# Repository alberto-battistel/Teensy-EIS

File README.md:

# Teensy-EIS

At the moment this git is still slightly chaotic, but it is getting better.
The idea is to use the two ADCs of the Teensy 3.6 (pjrc.com) to aquire data and the DAC to create the perturbation (sinus/multisine) to work as an impedance analyzer. All controlled by a PC using Python, which also make the analysis part. We have an analog front-end for voltage shift (Teensy works 0-3.3V both ADC and DAC) to connect to the real potentiostat. This is tested and works.

## 1 - ADC-DAC
ADC-DAC.ino and readFromPython.py work together. They are THE Teensy-EIS programs. CalculateParameters.m helps to make the parameters to feed in Python.

## 2 - Examples
In ADC-DAC there are examples of the part of the ADC-DAC.ino. DAC is for the DAC and PingPong manages the serial communication with the PC. They are more or less the most updated or the same as in ADC-DAC.ino.

## 3 - Regarding the DAC
The signal for the DAC is generated through a Matlab/GNU Octave/Scilab script. (Generate_DAC_vector). 

## 4 - Analog front-end
In analog front-end there is all about the core of the voltage shift. All the analog interface with the instrument is based on four INA128. They are very flexible pieces. There is no schematic for the power stage and activation of the signal line, but the elements are in the two PDF.

## 5 - Control flow
In Schematics there are the diagrams of the programs. At the moment only the part for the aquisition, which is the most complex. In summary, the Teensy can aquire infinite amount of data which are streamed in blocks to the PC. Python can handle easily several milions data points. 

## 6 - pointer?
pointers-reference-test contains a couple of examples about passing by reference or by pointer to a function. Not fundamental for the rest, just to remember.

------------------------------------
# Version list:

## Version 1.00
Fully operational tidy up version.

## Version 0.99
Fully operational prototype, both for the programing side and for the analog side. 

------------------------------------
# Bug List:
So we can keep track of what needs to be fixed

-To be filled (Priority: 1)

------------------------------------
# Future Feature List:

## Version 1.1?
what shall we implement next?

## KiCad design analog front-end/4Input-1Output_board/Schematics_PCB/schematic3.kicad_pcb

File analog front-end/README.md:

# Analog front-end
The analog front-end interfaces the *Teensy* to the instrument (potentiostat). It serves as conditioning of the signals. It mainly provides low impedance for the inputs, level shift (*Teensy* is 0-3.3V), and some degree of rejection for ground loops (still to understand a bit better). It also features an independent power stage (USB compatible) to handle bipolar signals.

## Signal conditioning
At the moment the conditioning is build on 4 **INAs 128** (Instrumentation amplifiers) from Texas Instruments. They are flexible building blocks featuring low noise, low distortion, easy level shift, and high impedance inputs (10 GOhm). Two INAs are used to buffer, level shift, and shrink the DAC (digital to analog converter) of the *Teensy* and the other two are for level shifting of the inputs of the two ADCs (analog to digital converter). 
Analog filtering can be easily attached to the INAs.
**4Input-1Output_board** contains the full design (schematics and printed circuit board layout with bill of components) to build up the signal conditioning part. It is a very flexible board. We also employ it for *additional reference electrode probes* in electrochemical cells or to *break groud loops*.

## Power
The power stage is based on a **DC-DC converter** (*NMA0515SC* from Murata). It takes 5 V as input and provides +/- 15 V. It may be connected to the *Teensy* and take power from the same USB cable, but we did not test this yet. The bipolar voltage is used to power the INAs. The positive rail is also used to hold a normally open **signal relay** (*MT2 Relay* from AXICOM). This relay is controlled by a digital pin of the *Teensy* through a transistor (*2N3904*) and it is necessary to cut the DAC line from the *Teensy* toward the instrument so that unwanted signals cannot be injected (for example when you turn on the *Teensy*...).

## State of the material
At the moment the schematics and the PCB layout signal conditioning part is available in **4Input-1Output_board**, but we may come out with a more practical design later. 
**Complete_analog_front-end.pro** (*KiCAD project* in **Design_schematics**) contains the *functional design* of the project with the fundamental connections between the *Teensy* and the analog front-end and the power stage.

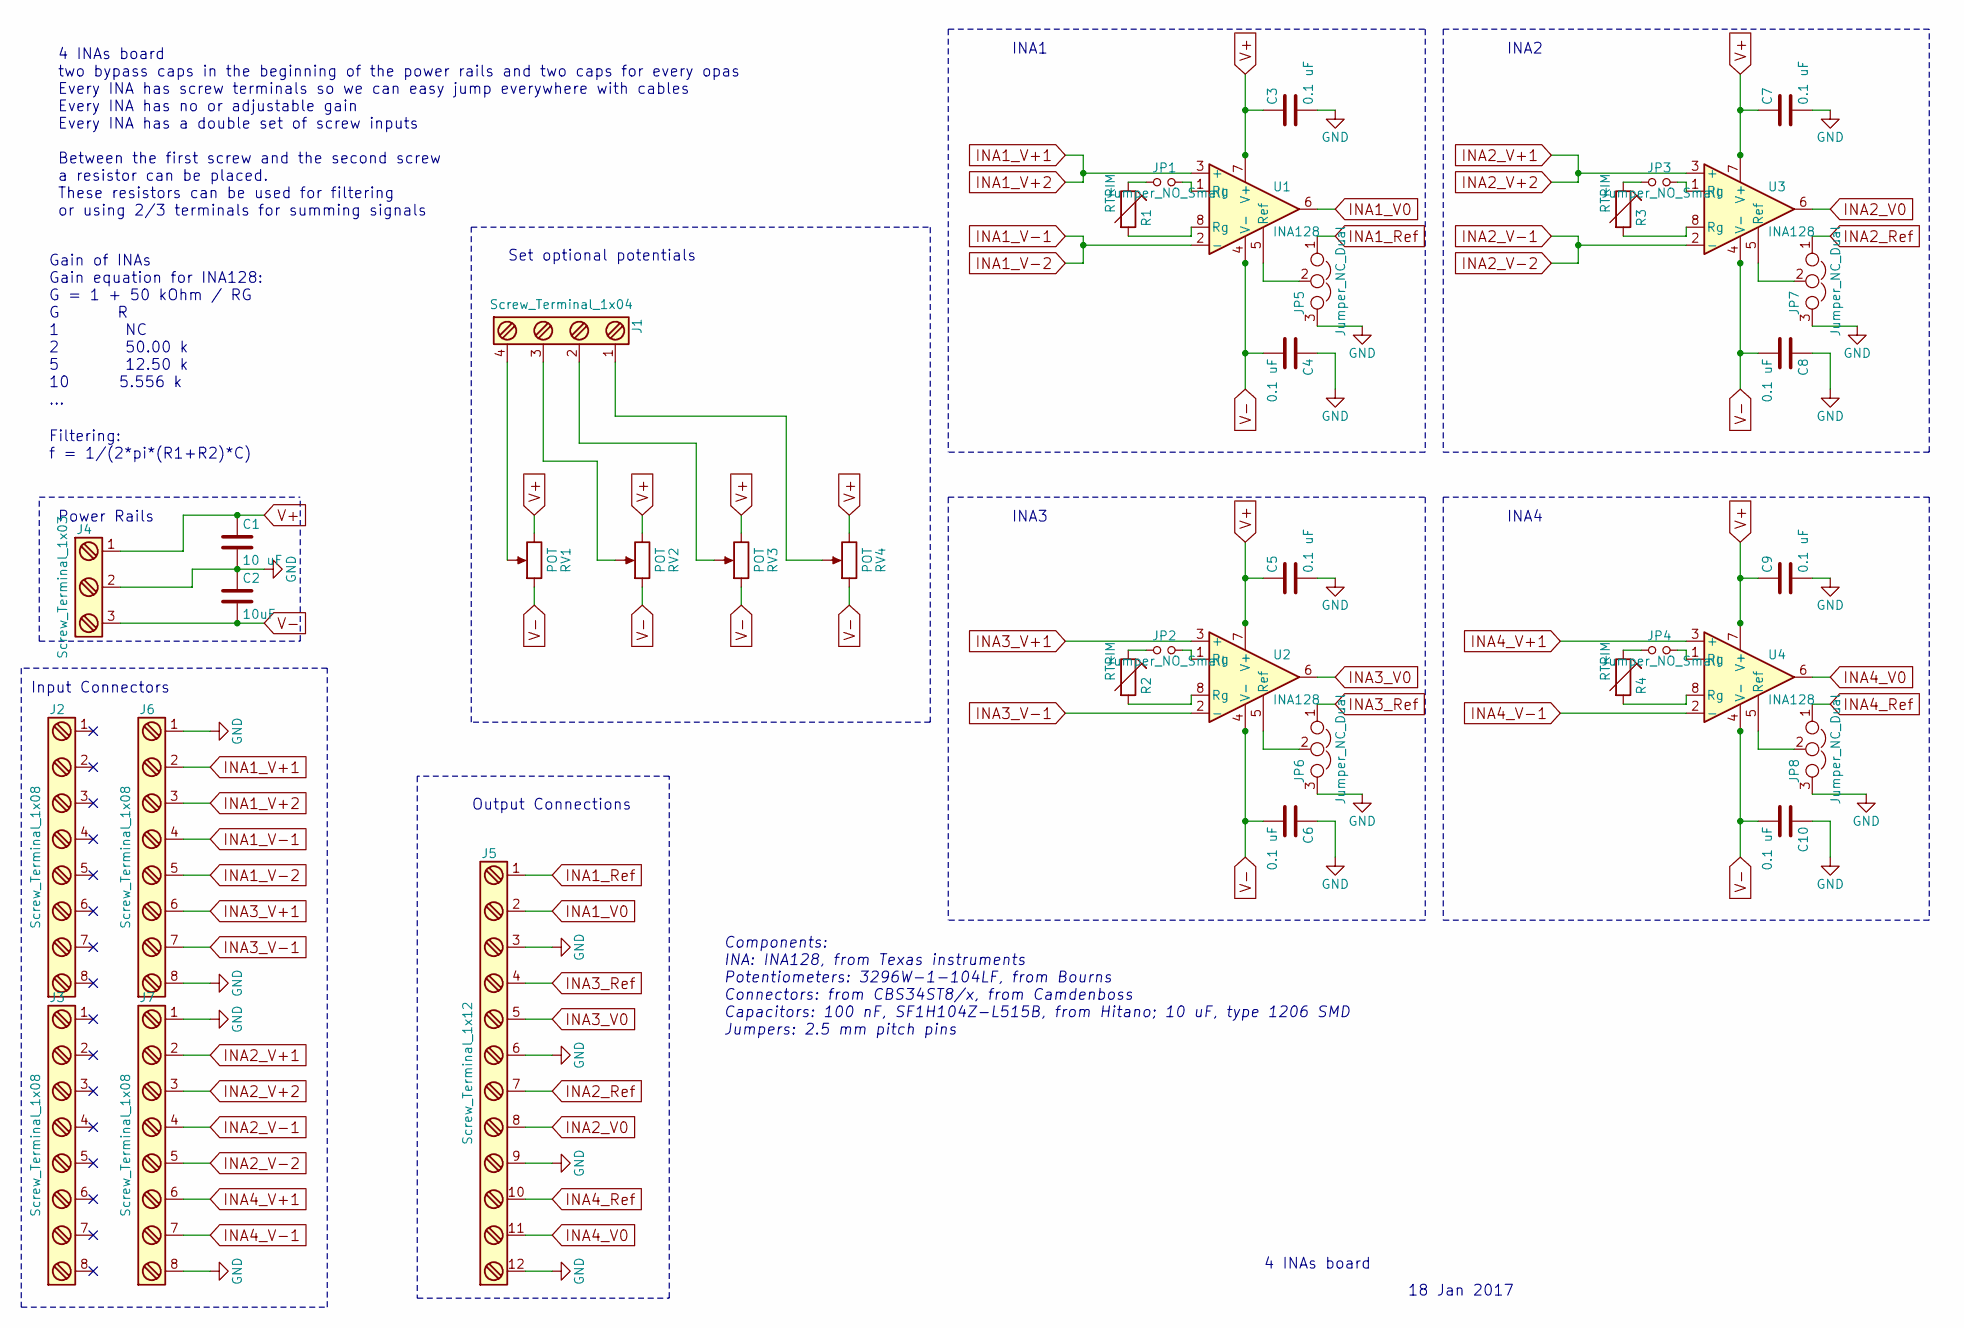
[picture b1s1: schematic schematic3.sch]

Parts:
C1: 10 uF; C_0603_HandSoldering
C2: 10uF; C_0603_HandSoldering
C3, C4, C5, C6, C7, C8, C9, C10: 0.1 uF; C_Disc_D5.0mm_W2.5mm_P5.00mm
J1: Screw_Terminal_1x04; Camdenboss_Screw_terminal_4x9.5mm
J2, J3, J6, J7: Screw_Terminal_1x08; Camdenboss_Screw_terminal_8x9.5mm
J4: Screw_Terminal_1x03; Camdenboss_Screw_terminal_3x9.5mm
J5: Screw_Terminal_1x12; Camdenboss_Screw_terminal_12x9.5mm
JP1, JP2, JP3, JP4: Jumper_NO_Small; JST_EH_B02B-EH-A_02x2.50mm_Straight
JP5, JP6, JP7, JP8: Jumper_NC_Dual; JST_EH_B03B-EH-A_03x2.50mm_Straight
R1, R2, R3, R4: RTRIM; Potentiometer_Bourns_3296W_3-8Zoll_Inline_ScrewUp
RV1, RV2, RV3, RV4: POT; Potentiometer_Bourns_3296W_3-8Zoll_Inline_ScrewUp
U1, U2, U3, U4: INA128; DIP-8_W7.62mm_Socket

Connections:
GND: C1.2, C2.1, C3.2, C4.1, C5.2, C6.1, C7.2, C8.1, C9.2, C10.1, J4.2, J5.3, J5.6, J5.9, J5.12, J6.1, J6.8, J7.1, J7.8, JP5.3, JP6.3, JP7.3, JP8.3
INA1_Ref: J5.1, JP5.1
INA1_V0: J5.2, U1.6
INA1_V+1: J6.2, J6.3, U1.3 (+)
INA1_V-1: J6.4, J6.5, U1.2 (-)
INA2_Ref: J5.7, JP7.1
INA2_V0: J5.8, U3.6
INA2_V+1: J7.2, J7.3, U3.3 (+)
INA2_V-1: J7.4, J7.5, U3.2 (-)
INA3_Ref: J5.4, JP6.1
INA3_V0: J5.5, U2.6
INA3_V+1: J6.6, U2.3 (+)
INA3_V-1: J6.7, U2.2 (-)
INA4_Ref: J5.10, JP8.1
INA4_V0: J5.11, U4.6
INA4_V+1: J7.6, U4.3 (+)
INA4_V-1: J7.7, U4.2 (-)
unnamed: J1.1, RV4.2
unnamed: J1.2, RV3.2
unnamed: J1.3, RV2.2
unnamed: J1.4, RV1.2
unnamed: JP1.1, R1.1
unnamed: JP1.2, U1.1 (Rg)
unnamed: JP2.1, R2.1
unnamed: JP2.2, U2.1 (Rg)
unnamed: JP3.1, R3.1
unnamed: JP3.2, U3.1 (Rg)
unnamed: JP4.1, R4.1
unnamed: JP4.2, U4.1 (Rg)
unnamed: JP5.2, U1.5 (Ref)
unnamed: JP6.2, U2.5 (Ref)
unnamed: JP7.2, U3.5 (Ref)
unnamed: JP8.2, U4.5 (Ref)
unnamed: R1.2, U1.8 (Rg)
unnamed: R2.2, U2.8 (Rg)
unnamed: R3.2, U3.8 (Rg)
unnamed: R4.2, U4.8 (Rg)
V+: C1.1, C3.1, C5.1, C7.1, C9.1, J4.1, RV1.3, RV2.3, RV3.3, RV4.3, U1.7 (V+), U2.7 (V+), U3.7 (V+), U4.7 (V+)
V-: C2.2, C4.2, C6.2, C8.2, C10.2, J4.3, RV1.1, RV2.1, RV3.1, RV4.1, U1.4 (V-), U2.4 (V-), U3.4 (V-), U4.4 (V-)

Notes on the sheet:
Gain of INAs Gain equation for INA128: G = 1 + 50 kOhm / RG G R 1 NC 2 50.00 k 5 12.50 k 10 5.556 k ...
INA1
Power Rails
4 INAs board two bypass caps in the beginning of the power rails and two caps for every opas Every INA has screw terminals so we can easy jump everywhere with cables Every INA has no or adjustable gain Every INA has a double set of screw inputs Between the first screw and the second screw a resisto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
Set optional potentials
Filtering: f = 1/(2*pi*(R1+R2)*C)
INA2
INA4
4 INAs board
18 Jan 2017
INA3
Input Connectors
Output Connections
Components: INA: INA128, from Texas instruments Potentiometers: 3296W-1-104LF, from Bourns Connectors: from CBS34ST8/x, from Camdenboss Capacitors: 100 nF, SF1H104Z-L515B, from Hitano; 10 uF, type 1206 SMD Jumpers: 2.5 mm pitch pins

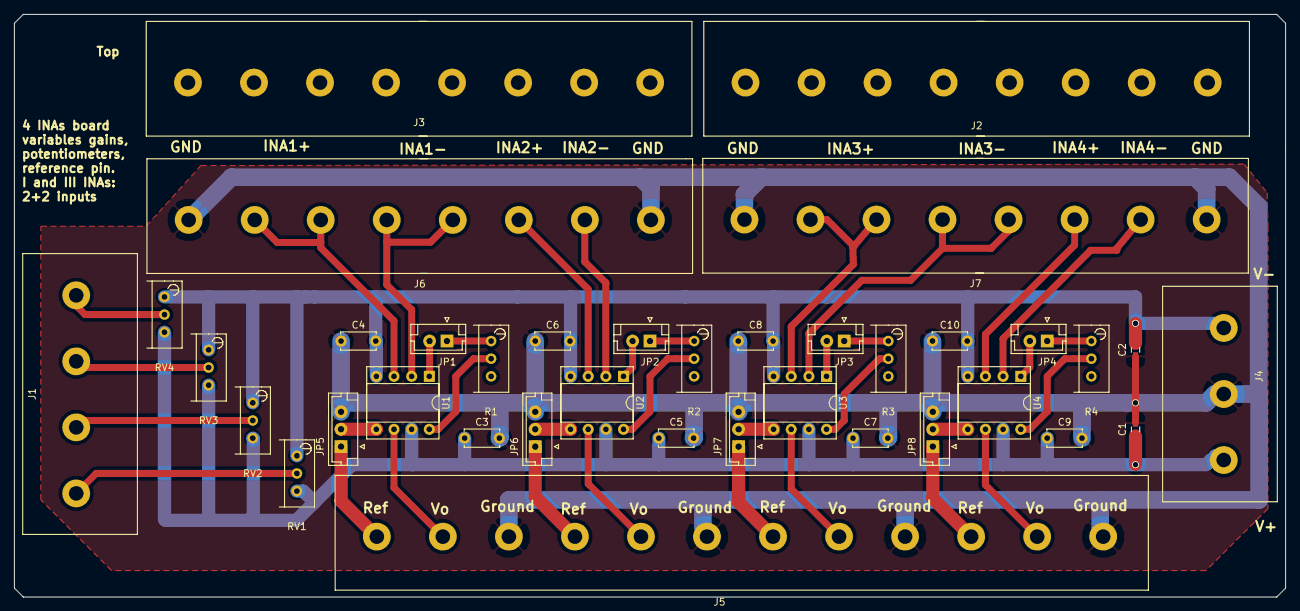
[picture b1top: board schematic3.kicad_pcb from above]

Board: 2 copper layers, 182.9 x 83.8 mm, 37 parts (0 on the bottom side), 39 nets.

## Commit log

2017-08-25 first commit, really the previous was an error
2017-08-26 justTest and readFromPython can pass data
2017-08-27 put a bit of order and add example for DAC
2017-08-27 updated datalogger_2ch with byte stream
2017-08-28 ADC-DAC: DAC and ADC work fine together, but there are some problems with the stream of data toward python.
2017-08-28 ADC-DAC starts to work, teensy streams to python, but I lose synchronization sometimes
2017-08-29 ADC-DAC works fine with one ADC, python catches all the stream
2017-08-30 Test commit by Chris
2017-08-30 ADC-DAC now can stream both channels, but StreamData needs to be corrected...
2017-08-31 collecting things into function in ADC-DAC
2017-08-31 I implemented pointers in ADC-DAC, but i dont understand what I am streaming. If both adc are connected I see two nice equal sinus. If only one of the two is disconnected I see strange noise.I have n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
2017-09-04 Starting to collect things for the analog front-end.
2017-09-04 schematics
2017-09-05 Added some organizational stuff(bug list, future feature list), to help contributors know where to focus.
2017-09-05 Create development_list.txt
    list of things to implement
2017-09-05 PingPong old style
2017-09-05 fix Parameters passing, but I do not understand header and source files.
2017-09-06 Update development_list.txt
    modified development_list.txt adding the transistor part
2017-09-06 Implemented header file for PingPong, not properly done (I don't have a cpp file), but it works.
2017-09-06 DAC.h done and working
2017-09-06 I did a mess with the file in the previous commit and now I fixed. I also moved PingPong in ADC-DAC.
2017-09-06 I had a pc failure, but now I am back. I integrated PingPong.h into ADC-DAC.ino. Ready for the loops.
2017-09-06 All the functions definition have been moved out of ADC-DAC.
2017-09-06 Create LICENSE
    Added LICENSE
2017-09-06 fixed a couple of bugs
2017-09-06 added DefaultParameters.h. ADC-DAC.ino can loopgit add . maybe some comments are missing or needed...
2017-09-06 Teensy and Python are looping together! Still very rough, but working.
2017-09-07 I need to fix python to calculate Z...
2017-09-07 python and teensy works together, I made a matlab script to calculate the Paramerters. I have problems with the PDB, I think.
2017-09-07 Teensy and python work together. CalculateParameters.m calculates the parameters. Some frequencies come very nice (ADC 200, 20, 8, and 2 kHz) some less.There are loss of data at low frequencies (belo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
2017-09-08 It should really be wroking now. There was still the problem with the size of the DMAbuffer in the streaming. I do not know where that modification went.
2017-09-08 Many small changes, getting close to a good Nyquist plot. Fingers crossed
2017-09-09 Various fixes, implemented during grueling evening of testing. Successfully obtained reasonable results.
2017-09-10 Big cleaning. Add all the material for the analog front-end (INAs board). Version 1.00git add .!
2017-09-21 Moved filter capacitor on the second INA stage of the DAC. Now it filters at 200-500 Hz.
2017-09-23 Started KiCAD schematics of all the analog part of the Teensy-EIS.
2017-10-08 Functional diagram of the project is finished. Few details are missing: pull-down resistor, position of the filter capacitor...
2017-10-08 Update README.md of analog front-end.
2017-11-15 Fix shutdown. Now there is a 47 kOhm pulldown resitor and the relayPin goes low.
2017-11-15 Issue #2: define function to communicate with Teensy. Next it is to implement module.
2017-11-16 Made an example script to see how to communicate with Teensy. There are some problems: I cannot restart Teensy from Python and I need to improve the module handling for debugging easy communications.
2017-11-16 Issue #2, I made an example script to see how to communicate with Teensy. There are some problems: I cannot restart Teensy from Python and I need to improve the module handling for debugging easy com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
2017-12-14 Issue#2: Now Python can find the dev value of Teensy. Still problems when Teensy shutdown. There are some extra python scripts but they do nothing.
